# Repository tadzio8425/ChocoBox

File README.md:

<div>
  <h1>     ChocoBox</h1>
</div>

### Environment replicator for cocoa fermentation:
- Electronic system that replicates a real life environment. Includes:
  - Continous environmental humidity and temperature measurement
  - Real-time control of both humidity and temperature
  - Spline generation to emulate environmental changes
  - Intuitive set-up and data collection via .txt files
- Backend developed using the Arduino Framework and an ESP32 development board.
- Frontend mobile app developed using the Expo Framework and React-Native.
- Developed in the *Universidad de Los Andes* for the *Biomicrosystems research group*.

## Developed by: 
<ul>
  <li>Juan Sebastián Ortega (https://github.com/tadzio8425)</li>
  <li>Nicolás Correal (https://github.com/Correaln47)</li>
</ul>

## Quickstart
### 1. Setting-up the files...

#### i. Creating the files
The ChocoBox system uses three *.txt* files inside a **MicroSD Card** in order to function, these files are *environment.txt*, *spline.txt* and *datalog.txt*. Altough these files have the *.txt* format, their content is designed to be read as a *.csv*. For the proper functioning of the system, it is **obligatory** for the files to be named exactly like this. If it is your first time using ChocoBox, or if you are resetting the system, please delete all previous files from the SD Card and create three empty *.txt* files.

<p align="center">
   <i>a. Contents of the MicroSD Card</i>
</p>

#### ii. Setting-up the environment
The environment to be replicated can be easily set in the *environment.txt* file. In order to to this, simply write the *csv* headers in the first row. These headers should be **hour, temperature, humidity**. Then, following the header order, write the desired values for specific hours in each new line. For example, this file replicates an environment for 96 hours, setting new desired values each 24 hours. There is no inverval restriction, neither there is a necessity for an interval, just make sure that the next hour is always greater than the previous one! **Please make sure that there are no extra new lines or blank spaces!**

<p align="center">
   <i>b. Example of an environment.txt file</i>
</p>

#### iii. Joining the dots
In order to replicate how these variables behave smoothly in nature, a cubic spline algorithm is used in order to fill the gaps between the dots set in *environment.txt*. The results of this algorithm are saved by the microcontroller in *spline.txt*, so this file must not be modified in any way by the user. If the **reference values** shown by the system are not logical, please check the *spline.txt* file. A *spline.txt* with **Nan** values or other errors indicates that *environment.txt* was wrongly formated! 

<p align="center">
   <i>c. Example of a correctly generated spline.txt file</i>
</p>

#### iv. Step by step
A fundamental part of the spline algorithm is the **step**, this value determines the interval for intermediate points to be calculated and also for data capture. For example, a step of **30 minutes** will make the system update its reference values and save its environmental data each, well, 30 minutes. The smaller the step, the more data will be captured and the smoother the system will be. **Beware of using extremely small steps, as they may lead to a memory overflow in the ESP32!** The **step can be modified by the user**, this will be explained in a further section.

#### v. Getting the data
All environmental data captured by the sensors is saved in *datalog.txt*, which is automatically updated by the microcontroller. This file includes the sensed information of each individual humidity and temperature sensor, captured each **step**. This file follows the order of the following headers: **time(min), tempA(degC), tempB(degC), tempC(degC), tempD(degC), humidLeft(%), humidRight(%)**

The presence of **Nan** values in this file may indicate a sensor malfunction!

<p align="center">
   <i>d. Example of a correctly generated datalog.txt file</i>
</p>

## 2. PCB Connections
Handling the PCB should be avoided at all costs. However, in the case that something has gone wrong or a new interface/sensor needs to be added, the following connection diagram should be **strictly** followed. All cables are marked with their respective signal.

| PCB Overview |
| --- |
|   |

| DS18B20 (Temp) | DHT22 (Hum) | MicroSD |
| --- | --- | --- |
||||

| I2C (LCD Screen and Clock) | Humidifier and Heater Relay | 12V and WaterLevel |
| --- | --- | --- |
||||

## 3. Cable management
ChocoBox uses an electric extension to power itself, the extension input should be conected directly to the power socket. This extesion has 3 available output sockets, of which only 2 are actually used. One of the sockets must me connected to the **resistor cable**, which handles the power given to the heating resistors. The second socket must be connected to a **12V-2A** power supply that powers the electronics. The output of the power supply is a **jack connector** which goes directly into the PCB box. Remember that you may find the extension sockets on the floor, behind the resistor wooden holder. Please make sure that all major cables are correctly pluged-in before performing any test, also **do not handle cables under any circumstance unless the resistors are totally cold**.

- To completely **TURN-OFF** the system, you only need to unplug the extension input from the power socket.

## 4. Operating the system
Once everything is pluged-in, the system should start to work autonomously. This means that the desired values from *environment.txt* will be replicated inside the box, following the intermidiate points generated in *spline.txt* and the actual sensed values will be saved each **step** in *datalog.txt*.

### i. Monitoring 01: LCD Screen
The most straigth-forward method to monitor the system is by looking at its **20x4 LCD Screen**. This screen depicts the following data, line by line:
  1. **Humidity**: Displays the current humidity average inside the box in (%).
  2. **Temperature**: Displays the current temperature average inside the box in (°C).
  3. **Ref**: Displays the reference values that the system should be trying to achieve in that specific moment.
  4. **Time**: Displays how much time has the system been on a specific fermentation cycle. This timer **DOES NOT** reset when the system is disconnected, as it is programmed to retake fermentation despite a possible temporal failure. However, it can be reset **manually**.

| LCD Screen |
| --- |
|   |

### ii. Connecting to the ESP32 via WiFi
The ESP32 is set in *AP* mode, which means that it acts as an *Access Point* (A.K.A. its own WiFi network). In order to connect, simply search for the network called **ChocoBox** and establish a connection using the **secret password**. It is **important** that this password is only given to authorized staff, otherwise, a fermentation cycle could be jeopardized.

- **Once connected to the _ChocoBox_ network, the ESP32 can be accessed using its IP Address which will always be:**
- **192.168.1.1**

| The ChocoBox Network |
| --- |
|   |

### iii. Monitoring 02: Rest API

| Root: / |
| --- |
|   |

Accessing the root of the rest API via any browser (192.168.1.1/) displays the current state of its variables. Thus, ChocoBox can be monitored in real time without the need of an external app.

| Request | Path  | Description |
| --- | --- | --- |
| GET | /datalog  | Downloads the dataLog up to the latest measurement.|
| POST | /environment | Uploads an environment.txt to the system. When the system is reset, the uploaded file will set a new curve to follow. The included python script displays its POST format.|
| POST | /step | Updates the step of the spline algorithm. Its content must be a number that represents a certain number of hours (at least 0.05).|

### iv. Monitoring 03: App
An app was developed using the Expo Framework in order to unify all the API Requests in an intuitive and user friendly interface.

| Init Page| Main Page | Data Module |
| --- | --- | --- |
|  |  | |

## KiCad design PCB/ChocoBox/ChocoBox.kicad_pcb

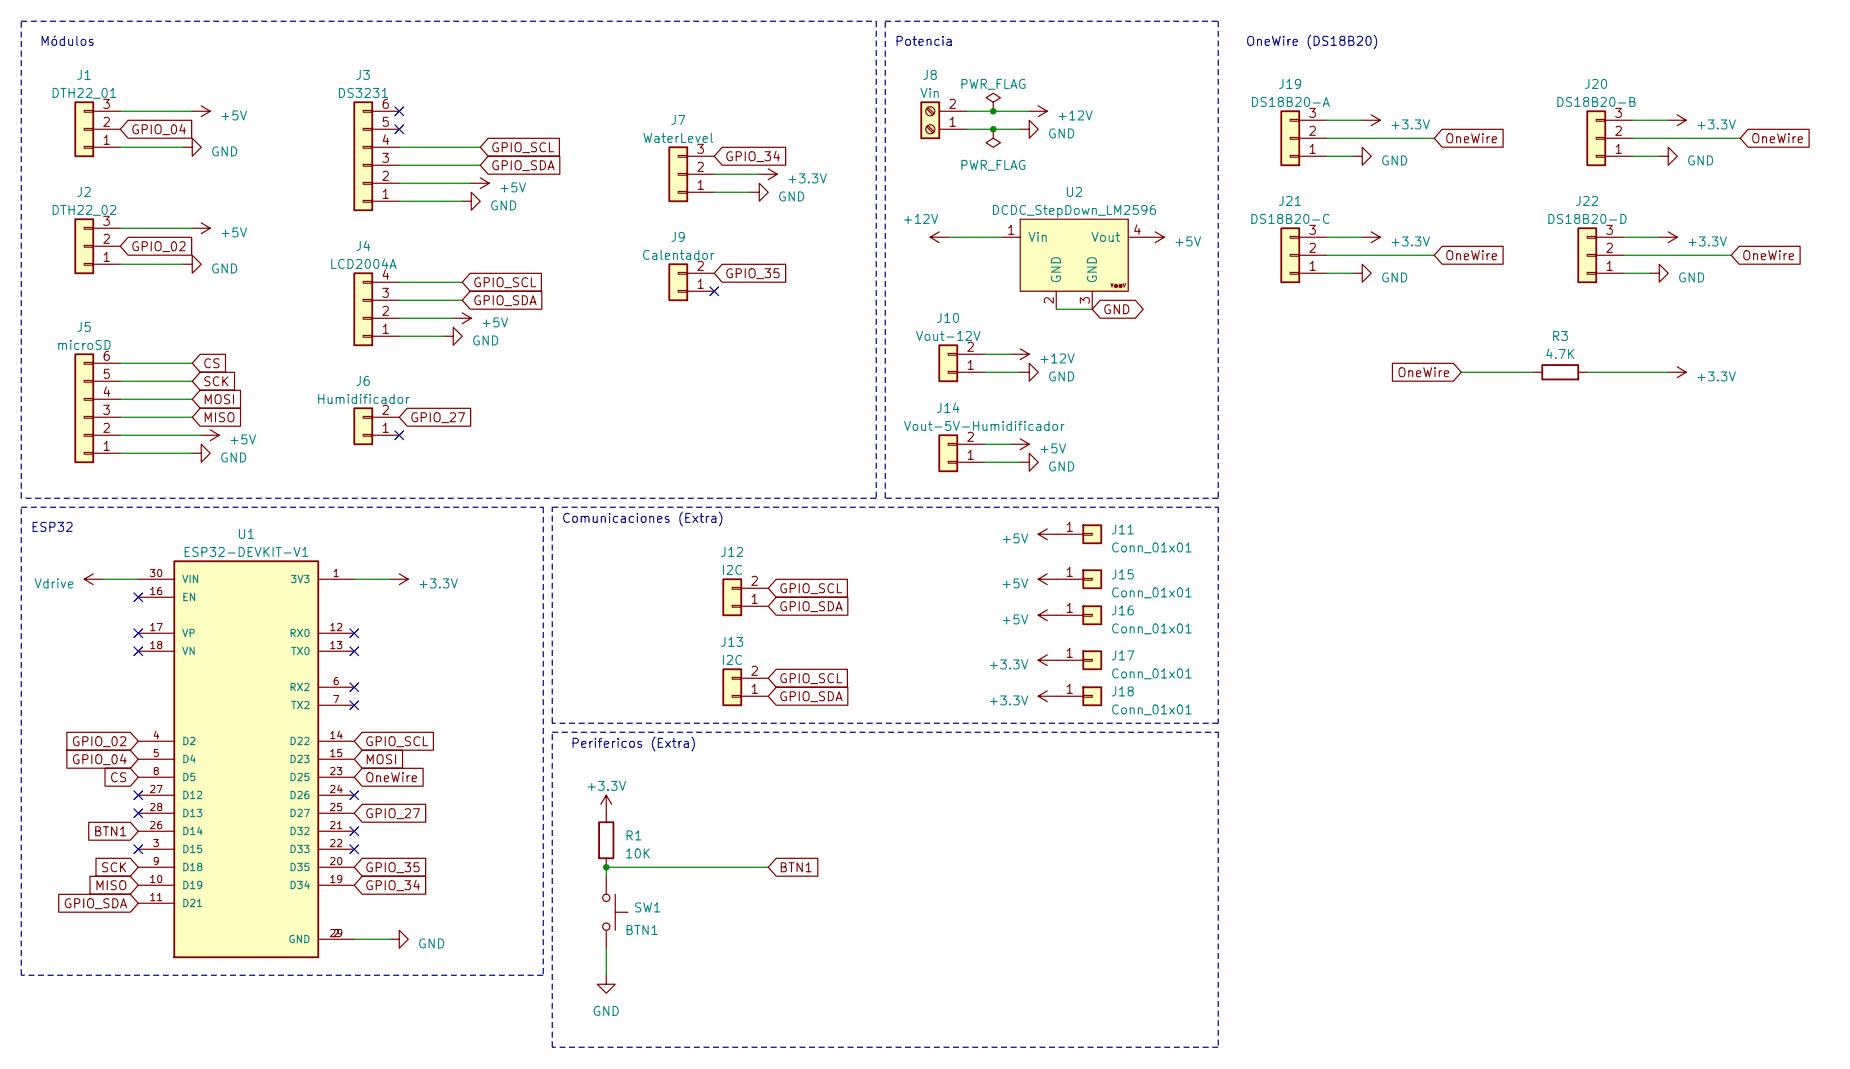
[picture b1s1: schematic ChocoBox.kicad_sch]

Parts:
J1: DTH22_01; PinSocket_1x03_P2.54mm_Vertical
J2: DTH22_02; PinSocket_1x03_P2.54mm_Vertical
J3: DS3231; PinSocket_1x06_P2.54mm_Vertical
J4: LCD2004A; PinSocket_1x04_P2.54mm_Vertical
J5: microSD; PinSocket_1x06_P2.54mm_Vertical
J6: Humidificador; PinSocket_1x02_P2.54mm_Vertical
J7: WaterLevel; PinSocket_1x03_P2.54mm_Vertical
J8: Vin; TerminalBlock_Phoenix_MKDS-1,5-2-5.08_1x02_P5.08mm_Horizont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
J9: Calentador; PinSocket_1x02_P2.54mm_Vertical
J10: Vout-12V; PinSocket_1x02_P2.54mm_Vertical
J11, J15, J16, J17, J18: Conn_01x01; PinSocket_1x01_P2.54mm_Vertical
J12, J13: I2C; PinSocket_1x02_P2.54mm_Vertical
J14: Vout-5V-Humidificador; PinSocket_1x02_P2.54mm_Vertical
J19: DS18B20-A; PinSocket_1x03_P2.54mm_Vertical
J20: DS18B20-B; PinSocket_1x03_P2.54mm_Vertical
J21: DS18B20-C; PinSocket_1x03_P2.54mm_Vertical
J22: DS18B20-D; PinSocket_1x03_P2.54mm_Vertical
R1: 10K; R_Axial_DIN0207_L6.3mm_D2.5mm_P10.16mm_Horizontal
R3: 4.7K; R_Axial_DIN0207_L6.3mm_D2.5mm_P10.16mm_Horizontal
SW1: BTN1; PinSocket_1x02_P2.54mm_Vertical
U1: ESP32-DEVKIT-V1; MODULE_ESP32_DEVKIT_V1; PARTREV N/A
U2: DCDC_StepDown_LM2596; YAAJ_DCDC_StepDown_LM2596

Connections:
+3.3V: J7.2, J17.1, J18.1, J19.3, J20.3, J21.3, J22.3, R1.1, R3.2, U1.1 (3V3)
+5V: J1.3, J2.3, J3.2, J4.2, J5.2, J11.1, J14.2, J15.1, J16.1, U2.4 (Vout)
+12V: J8.2, J10.2, U2.1 (Vin)
BTN1: R1.2, SW1.1, U1.26 (D14)
CS: J5.6, U1.8 (D5)
GND: J1.1, J2.1, J3.1, J4.1, J5.1, J7.1, J8.1, J10.1, J14.1, J19.1, J20.1, J21.1, J22.1, SW1.2, U1.2 (GND), U1.29 (GND), U2.2 (GND), U2.3 (GND)
GPIO_02: J2.2, U1.4 (D2)
GPIO_04: J1.2, U1.5 (D4)
GPIO_27: J6.2, U1.25 (D27)
GPIO_34: J7.3, U1.19 (D34)
GPIO_35: J9.2, U1.20 (D35)
GPIO_SCL: J3.4, J4.4, J12.2, J13.2, U1.14 (D22)
GPIO_SDA: J3.3, J4.3, J12.1, J13.1, U1.11 (D21)
MISO: J5.3, U1.10 (D19)
MOSI: J5.4, U1.15 (D23)
OneWire: J19.2, J20.2, J21.2, J22.2, R3.1, U1.23 (D25)
SCK: J5.5, U1.9 (D18)
Vdrive: U1.30 (VIN)

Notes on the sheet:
Módulos
OneWire (DS18B20)
ESP32
Perifericos (Extra)
Comunicaciones (Extra)
Potencia

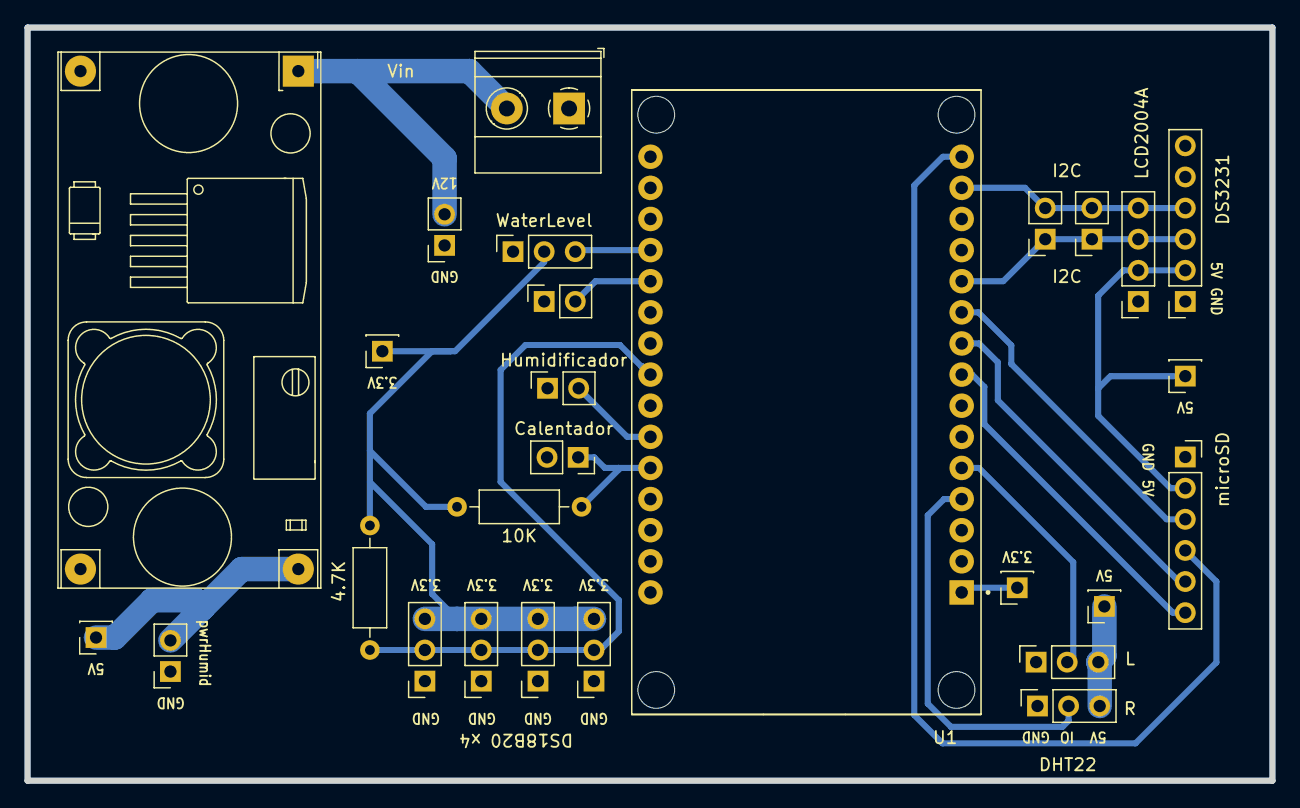
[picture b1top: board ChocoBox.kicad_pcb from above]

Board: 2 copper layers, 101.6 x 61.5 mm, 27 parts (0 on the bottom side), 17 nets.

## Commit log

2023-06-05 Commit inicial
2023-06-05 Conectividad a FireBase
2023-06-05 Humidificador agregado
2023-06-06 Sensorica en tiempo real
2023-06-06 Sensores DHT medidos
2023-06-06 Controlador humedad
2023-06-06 RTC implementado
2023-06-06 Pantalla LCD
2023-06-06 Controlador Temperatura
2023-06-06 Interpolación Cúbica
2023-06-06 Prueba interpolación cacao
2023-06-06 Carga Spline Firebase
2023-06-06 Almacenamiento en memoria flash
2023-06-06 arreglos memoria
2023-06-06 Humedad y temp en flash
2023-06-07 Actualización tiempo real
2023-06-07 arreglo tiempos (timer esp)
2023-06-07 Persistencia tiempo
2023-06-07 Tiempo logs
2023-06-07 Almacenamiento local ESP
2023-06-07 REST local
2023-06-07 Prueba REST Local
2023-06-07 Arreglos prueba rest
2023-06-07 Cambio tamaño buffer
2023-06-07 Reset funcionando
2023-06-07 modo dual
2023-06-07 Problemas de memoria arreglados
2023-06-07 arreglo memoria
2023-06-07 Modo sin WiFi activado
2023-06-07 Persistencia local y wifi
2023-06-08 Avance PCB y pines
2023-06-08 Inicio PCB
2023-06-25 offline
2023-06-25 pre offline
2023-06-25 Interpol en SD
2023-06-26 Monitoreo local listo!
2023-06-26 Display tiempo arreglado
2023-06-26 PCB V1 Terminada
2023-06-27 PCB terminada
2023-07-08 Controladores funcionando
2023-07-08 Arreglos control
2023-07-12 OneWire agregado y funcional
2023-07-13 Prueba con resistencia y moving average
2023-07-13 Prueba resistencia
2023-07-19 medición con todos los DS18B20
2023-07-20 avance HTML
2023-07-22 Temperatura funcionando
2023-07-22 Funciona
2023-07-22 Depurado spiffs
2023-07-25 Control LAN arreglado
2023-07-25 Cambio a controlador PID Bang-Bang
2023-07-25 PID Calibrado
2023-07-26 Interfaz principal App
2023-07-26 Reset con PUT
2023-07-27 App avanzada
2023-07-27 Arreglo color on/off
2023-07-27 Subir y descargar archivos!
2023-07-27 subir y descargar desde la app
2023-07-28 Primera APK
2023-07-29 Cambio de logo app
2023-07-29 Cambio formato datalog.txt
2023-07-31 Bug fix - App environment.txt
2023-07-31 Paso modificable
2023-08-02 Cambio step en la app
2023-08-02 Barra nivel de agua en app
2023-08-02 Beta
2023-08-02 Bug fix upload
2023-08-02 comma delete
2023-08-02 bug fix
2023-08-02 ignorar segunda línea
